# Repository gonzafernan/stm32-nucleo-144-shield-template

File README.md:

# STM32 Nucleo-144 Shield Template

A KiCad 8.0 template for designing shields compatible with STM32 Nucleo-144 development boards (NUCLEO-H743ZI, NUCLEO-F429ZI, NUCLEO-F746ZG and similar).

## What's Included

- Board outline matching the Nucleo-144 form factor
- Four shield connectors pre-placed and wired: CN8 (2×8), CN9 (2×15), CN7 (2×10), CN10/Zio (2×17)
- All STM32 GPIO ports (PA–PG) exposed as named nets
- Power rails: `+3V3`, `+5V`, `GND`, `AGND`, `AVDD`, `IOREF`, `VIN`

## Usage

1. In KiCad, open **File → New Project from Template** and select this template.
2. Add your components to the schematic using the pre-defined net labels.
3. Route your design within the ready-made PCB outline.

## License

MIT

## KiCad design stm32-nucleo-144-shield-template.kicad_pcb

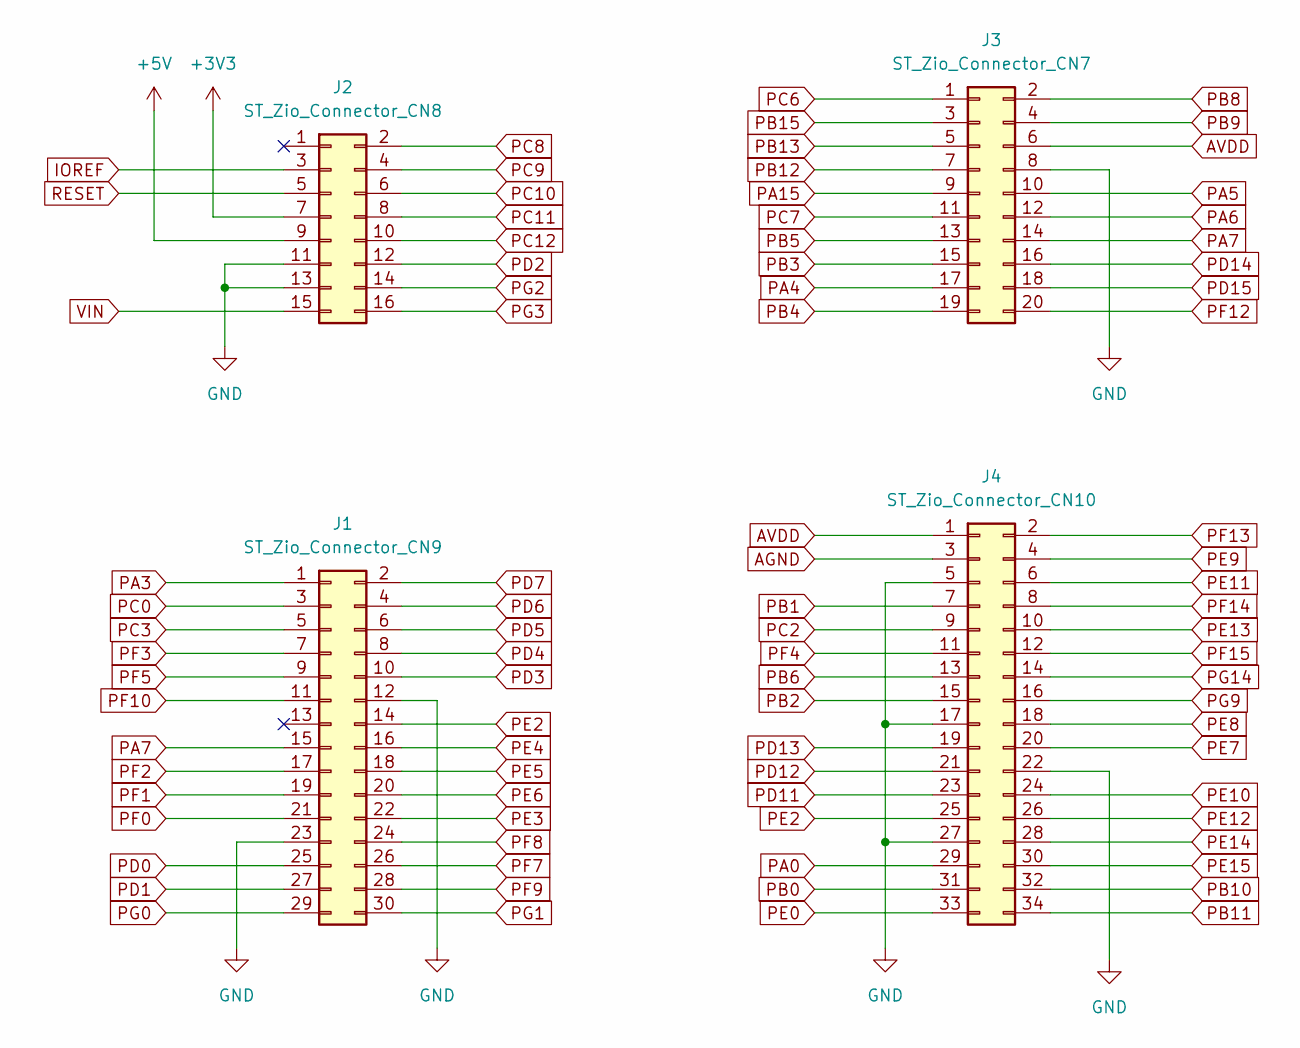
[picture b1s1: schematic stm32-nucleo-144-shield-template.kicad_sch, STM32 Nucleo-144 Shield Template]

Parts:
J1: ST_Zio_Connector_CN9; PinHeader_2x15_P2.54mm_Vertical
J2: ST_Zio_Connector_CN8; PinHeader_2x08_P2.54mm_Vertical
J3: ST_Zio_Connector_CN7; PinHeader_2x10_P2.54mm_Vertical
J4: ST_Zio_Connector_CN10; PinHeader_2x17_P2.54mm_Vertical

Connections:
+3V3: J2.7
+5V: J2.9
AGND: J4.3
AVDD: J3.6, J4.1
GND: J1.12, J1.23, J2.11, J2.13, J3.8, J4.5, J4.17, J4.22, J4.27
IOREF: J2.3
PA0: J4.29
PA3: J1.1
PA4: J3.17
PA5: J3.10
PA6: J3.12
PA7: J1.15, J3.14
PA15: J3.9
PB0: J4.31
PB1: J4.7
PB2: J4.15
PB3: J3.15
PB4: J3.19
PB5: J3.13
PB6: J4.13
PB8: J3.2
PB9: J3.4
PB10: J4.32
PB11: J4.34
PB12: J3.7
PB13: J3.5
PB15: J3.3
PC0: J1.3
PC2: J4.9
PC3: J1.5
PC6: J3.1
PC7: J3.11
PC8: J2.2
PC9: J2.4
PC10: J2.6
PC11: J2.8
PC12: J2.10
PD0: J1.25
PD1: J1.27
PD2: J2.12
PD3: J1.10
PD4: J1.8
PD5: J1.6
PD6: J1.4
PD7: J1.2
PD11: J4.23
PD12: J4.21
PD13: J4.19
PD14: J3.16
PD15: J3.18
PE0: J4.33
PE2: J1.14, J4.25
PE3: J1.22
PE4: J1.16
PE5: J1.18
PE6: J1.20
PE7: J4.20
PE8: J4.18
PE9: J4.4
PE10: J4.24
PE11: J4.6
PE12: J4.26
PE13: J4.10
PE14: J4.28
PE15: J4.30
PF0: J1.21
PF1: J1.19
PF2: J1.17
PF3: J1.7
PF4: J4.11
PF5: J1.9
PF7: J1.26
PF8: J1.24
PF9: J1.28
PF10: J1.11
PF12: J3.20
PF13: J4.2
PF14: J4.8
PF15: J4.12
PG0: J1.29
PG1: J1.30
PG2: J2.14
PG3: J2.16
PG9: J4.16
PG14: J4.14
RESET: J2.5
VIN: J2.15

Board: 2 copper layers, 4 parts (0 on the bottom side), 4 nets, no tracks yet.

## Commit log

2026-02-28 feat: initial template schematic and layout
2026-02-28 feat: add license to the project
